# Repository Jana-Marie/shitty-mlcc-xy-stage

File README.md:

# shitty-mlcc-xy-stage

This experiment aims to develop a mechanical super resolution stage for the OpenIRV project. The idea is to move the 60Hz 320x240px thermal imaging camera into four different positions during the recording to get a 15Hz 640*480px image. This would of course be ideal, but the image acquisition is not done every 16.6ms for an infinitely short time, but continuously, so the image will be "blurred". To cover the pixel-pitch of 17µm, the stage has to move about +-9µm in x- and y-direction.

This stage has also never been tested, I'm a sometimes lazy catgirl, meow!

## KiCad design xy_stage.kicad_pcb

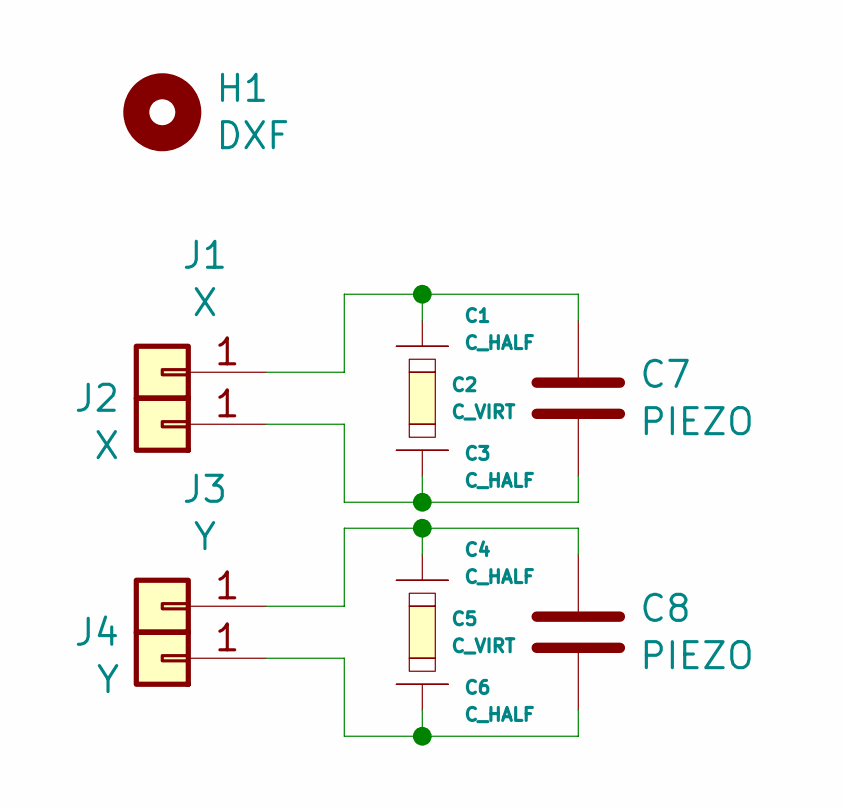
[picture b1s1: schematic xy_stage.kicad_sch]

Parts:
C1, C3, C4, C6: C_HALF; XY_pads
C2, C5: C_VIRT; XY_C_1812_3D_90
C7, C8: PIEZO; piezo_1.65x1.65x5
H1: DXF; xy_stage_outline
J1, J2: X; PinHeader_1x01_P2.54mm_Vertical_NOSILK
J3, J4: Y; PinHeader_1x01_P2.54mm_Vertical_NOSILK

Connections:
unnamed: C1.1, C7.1, J1.1
unnamed: C3.1, C7.2, J2.1
unnamed: C4.1, C8.1, J3.1
unnamed: C6.1, C8.2, J4.1

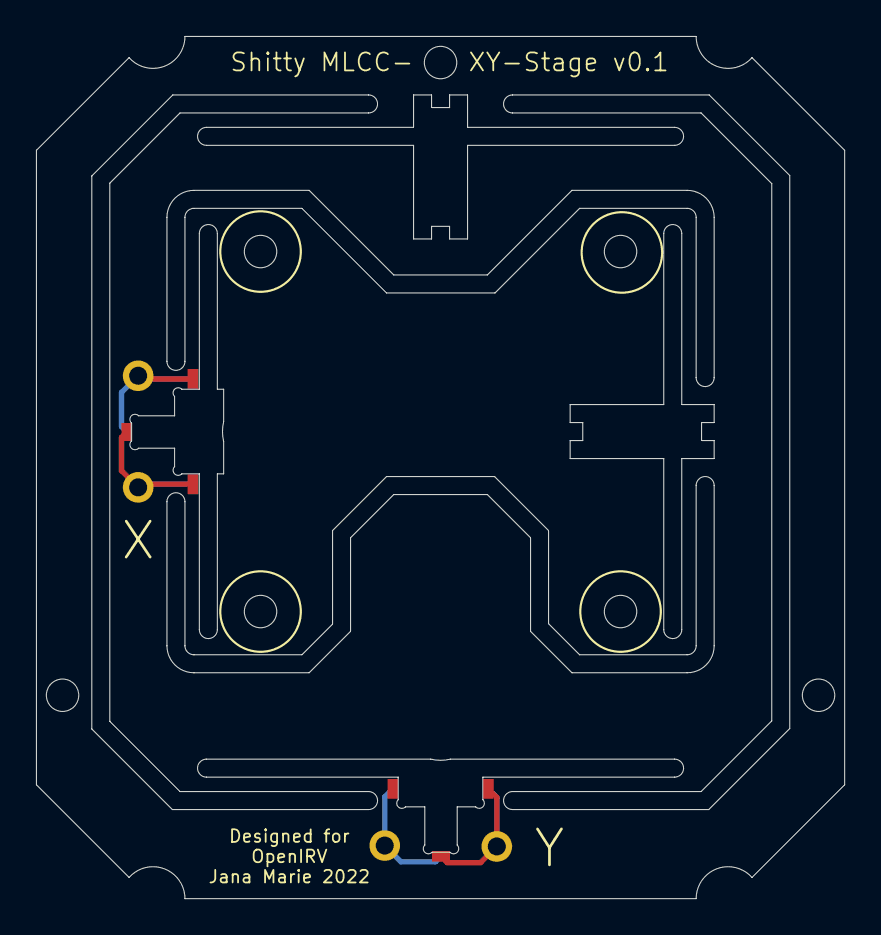
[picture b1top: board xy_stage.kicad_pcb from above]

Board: 2 copper layers, 44.9 x 47.9 mm, 13 parts (0 on the bottom side), 4 nets.

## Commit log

2022-01-22 added images
